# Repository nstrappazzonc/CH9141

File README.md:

# CH9141

Este es un IC que permite la comunicación Bluetooth a través de la comunicación serial de forma transparente. Lo impresionante de este chip es su simplicidad de conexión electrónica con apenas cuatro componentes y su simple configuración mediante comandos AT. Es diseñado y fabricado en china por [Jiangsu Heng Qin Ltd. (WCH)](http://www.wch-ic.com).

Existen diferentes formas de conectar el Bluetooth, en este repositorio nos centraremos en cómo se indica en el siguiente diagrama, para conocer más formas de conexión vea él [datasheet](https://github.com/nstrappazzonc/CH9141/blob/main/doc/CH9141DS1.PDF).

Podrá usar el IC para conectarse directamente a un PC o móvil, vea los siguientes [ejemplos](https://github.com/openwch/ch9141).

Puedes conseguir los IC o una placa de pruebas en la tienda oficial de [AliExpress](https://wchofficialstore.es.aliexpress.com/store/1100367542) o en [LCSC](https://www.lcsc.com).

De momento nos vamos a centrar en él [CH9141K](https://www.wch-ic.com/products/CH9141.html) que tiene unas prestaciones muy versátiles, entre ellas destacan las siguientes:

- Soporta el estándar Bluetooth BLE4.2 que es de bajo consumo.
- Llega hasta 100 metros de distancia.
- Soporta la configuración mediante comandos AT.
- Soporta diferentes modos: broadcast, host y slave.
- Permite una comunicación asíncrona de hasta 5Mbps.

## Componentes

Use los siguientes componentes para construir el circuito mínimo:

- Un IC CH9141K.
- Oscilador externo de 32MHz 10PPM y 12pF.
- Dos capacitores 2.2 uF.

## Proyectos relacionados

- [CH334 - HUB USB 2.0](https://github.com/nstrappazzonc/CH334)
- [CH340 - USB 2.0 to Serial](https://github.com/nstrappazzonc/CH340)
- [CH552 - 8-bits MCU - 8051](https://github.com/nstrappazzonc/CH552)

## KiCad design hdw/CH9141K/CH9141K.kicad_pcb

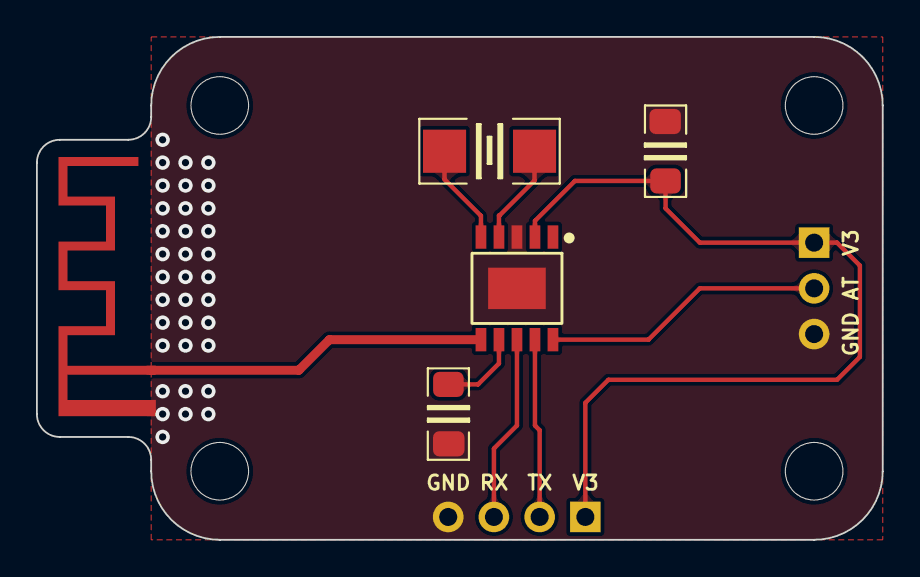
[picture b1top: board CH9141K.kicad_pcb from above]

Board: 2 copper layers, 47.0 x 27.9 mm, 11 parts (0 on the bottom side), 9 nets.

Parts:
AE2: Antenna_Shield; Texas_SWRA117D_2.4GHz_Right
C1, C2: 1uF; C1206
H1, H2, H3, H4: MountingHole; MountingHole_3.2mm_M3
J2: Conn_01x03; PinHeader_1x03_P2.54mm_Vertical
J3: Conn_01x04; PinHeader_1x04_P2.54mm_Vertical
U1: CH9141K; ESSOP-10
Y1: 32M; Crystal_SMD_5032-2Pin_5.0x3.2mm_HandSoldering

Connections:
AT: J2.2, U1.10 (AT)
GND: C1.2, C2.2, J2.3, J3.4, U1.0 (GND), U1.3 (GND)
unnamed: AE2.1 (A), U1.6 (ANT)
unnamed: C2.1, U1.7 (VINTA)
unnamed: U1.4 (X32MI), Y1.2
unnamed: U1.5 (X32MO), Y1.1
RXD: J3.3, U1.8 (RXD)
TXD: J3.2, U1.9 (TXD)
VCC: C1.1, J2.1, J3.1, U1.2 (VCC)

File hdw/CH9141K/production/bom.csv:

Designator,Footprint,Quantity,Value,LCSC Part #
AE2,Texas_SWRA117D_2.4GHz_Right,1,Antenna_Shield,
"C1, C2",C1206,2,1uF,
"H1, H2, H3, H4",MountingHole_3.2mm_M3,4,MountingHole,
J2,PinHeader_1x03_P2.54mm_Vertical,1,Conn_01x03,
J3,PinHeader_1x04_P2.54mm_Vertical,1,Conn_01x04,
U1,ESSOP-10,1,CH9141K,
Y1,Crystal_SMD_5032-2Pin_5.0x3.2mm_HandSoldering,1,32M,

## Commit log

2024-01-06 doc - update
2024-01-07 doc - update links
2024-03-09 wip - schematic & pcb for CH9141K
2024-03-10 poc - schematic & pcb for CH9141K
2024-03-12 update pcb design
2024-06-10 update doc
2024-10-23 Save changes at: 1729668673
2024-10-23 Save changes at: 1729669397
2024-10-23 Save changes at: 1729669522
2024-10-23 Save changes at: 1729669696
2024-10-23 Save changes at: 1729670069
2024-10-23 Save changes at: 1729675180
2024-10-23 Save changes at: 1729675340
2024-10-23 Save changes at: 1729675475
2024-10-23 Save changes at: 1729675500
2024-10-23 Save changes at: 1729675606
2024-10-23 Save changes at: 1729698466
2024-10-23 Save changes at: 1729714503
2024-10-24 Save changes at: 1729764661
2024-10-24 Save changes at: 1729772952
2024-10-24 Save changes at: 1729787424
2024-10-24 Save changes at: 1729790657
2024-10-24 Save changes at: 1729796362
